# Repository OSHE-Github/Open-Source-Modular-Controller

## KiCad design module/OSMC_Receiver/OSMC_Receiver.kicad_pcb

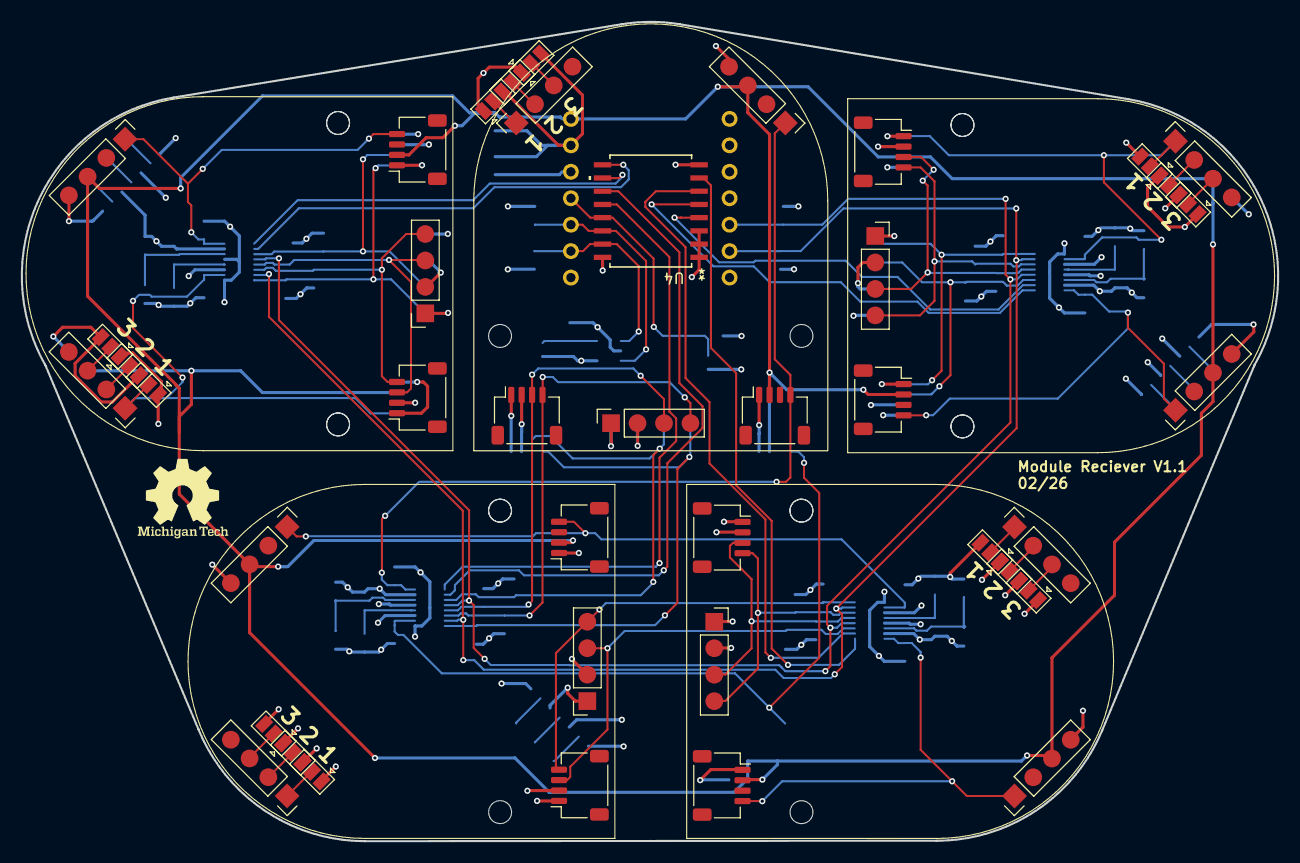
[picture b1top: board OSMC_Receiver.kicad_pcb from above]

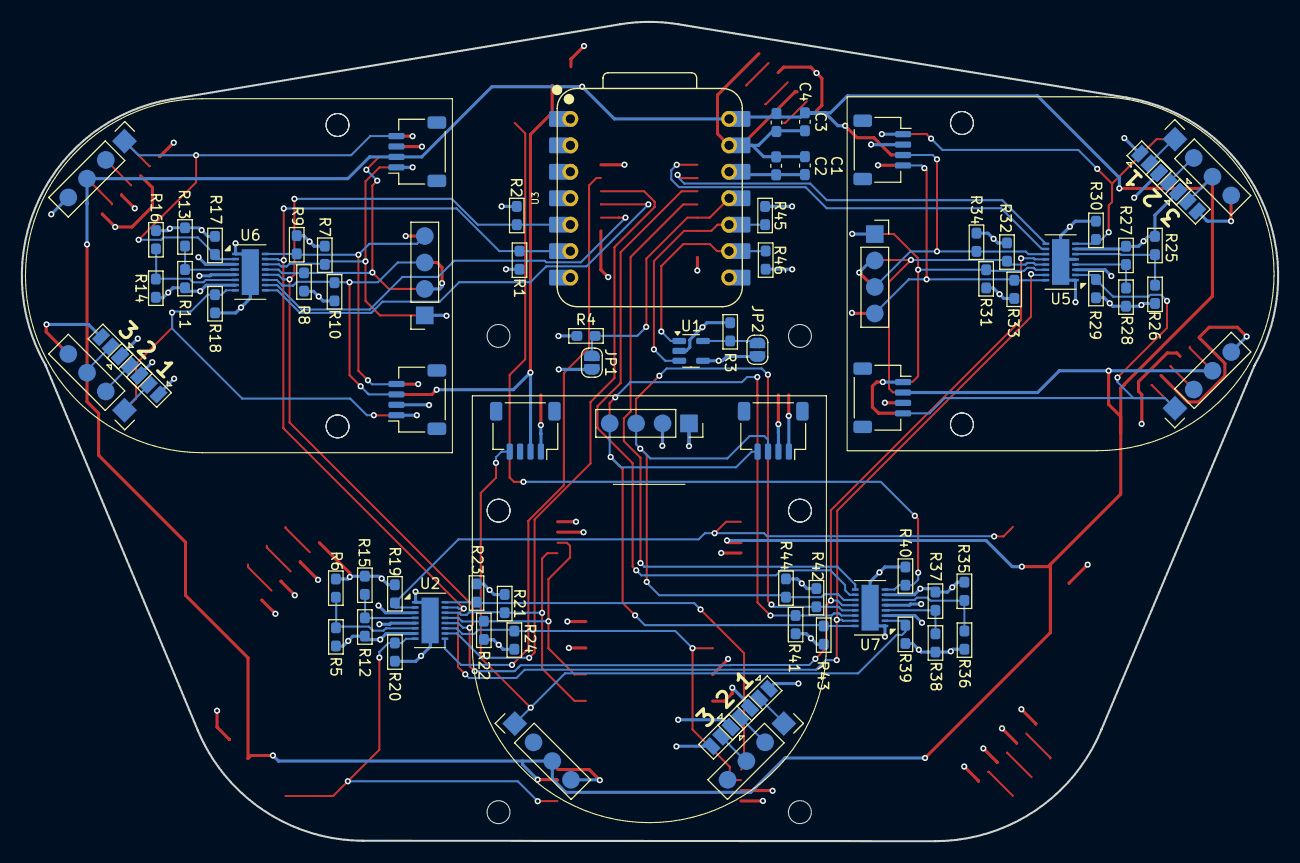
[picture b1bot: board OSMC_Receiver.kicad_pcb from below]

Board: 4 copper layers, 120.7 x 78.7 mm, 91 parts (70 on the bottom side), 73 nets.

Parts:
C1, C2: .1 u; C_0603_1608Metric_Pad1.08x0.95mm_HandSolder
C3, C4: C; C_0603_1608Metric_Pad1.08x0.95mm_HandSolder
JP1: int; SolderJumper-2_P1.3mm_Open_RoundedPad1.0x1.5mm
JP2: WP; SolderJumper-2_P1.3mm_Open_RoundedPad1.0x1.5mm
JP3, JP4, JP5, JP6, JP7, JP8, JP9, JP10, JP11, JP12, JP13, JP14, JP15, JP16, JP17, JP18, JP19, JP20, JP21, JP22, JP23, JP24, JP25, JP26: SolderJumper_3_Open; SolderJumper-3_P1.3mm_Open_Pad1.0x1.5mm
R1, R2, R7, R8, R9, R10, R17, R18, R19, R20, R21, R22, R23, R24, R29, R30, R31, R32, R33, R34, R39, R40, R41, R42, R43, R44, R45, R46: 10k; R_0603_1608Metric_Pad1.05x0.95mm_HandSolder
R3, R4: 100k; R_0603_1608Metric_Pad1.05x0.95mm_HandSolder
R5, R11: 976k; R_0603_1608Metric_Pad1.05x0.95mm_HandSolder
R6: 182k; R_0603_1608Metric_Pad1.05x0.95mm_HandSolder
R12: 1M; R_0603_1608Metric_Pad1.05x0.95mm_HandSolder
R13: 102k; R_0603_1608Metric_Pad1.05x0.95mm_HandSolder
R14: R; R_0603_1608Metric_Pad1.05x0.95mm_HandSolder
R15: 280k; R_0603_1608Metric_Pad1.05x0.95mm_HandSolder
R16: 0; R_0603_1608Metric_Pad1.05x0.95mm_HandSolder
R25, R27, R35, R37: 1000k; R_0603_1608Metric_Pad1.05x0.95mm_HandSolder
R26: 392k; R_0603_1608Metric_Pad1.05x0.95mm_HandSolder
R28: 523k; R_0603_1608Metric_Pad1.05x0.95mm_HandSolder
R36: 681k; R_0603_1608Metric_Pad1.05x0.95mm_HandSolder
R38: 887k; R_0603_1608Metric_Pad1.05x0.95mm_HandSolder
U1: 24AA02-OT; SOT-23-5
U2, U5, U6, U7: LTC4317; DFN-16-1EP_3x5mm_P0.5mm_EP1.66x4.4mm
U3: XIAO-ESP32-S3-DIP
U4: PCF8574DWR; DW16-L
U13, U14, U15, U16, U17, U18, U19, U20: OSMC Module Board; Module standard pin large outline

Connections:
+5V: C3.1, C4.1, U3.14 (5V), U13.10 (5V), U13.15 (5V), U14.10 (5V), U14.15 (5V), U15.10 (5V), U15.15 (5V), U16.10 (5V), U16.15 (5V), U17.10 (5V), U17.15 (5V), U18.10 (5V), U18.15 (5V), U19.10 (5V), U19.15 (5V), U20.10 (5V), U20.15 (5V)
/INT: JP1.1 (A), R4.2, U3.11 (PA6_A10_D10_MOSI), U4.13 (~INT)
/Modules/EN0: R18.2, U6.8 (ENABLE1), U13.12 (Det), U13.13 (Det)
/Modules/EN1: R17.2, U6.2 (ENABLE2), U15.12 (Det), U15.13 (Det)
/Modules/EN2: R20.2, U2.8 (ENABLE1), U16.12 (Det), U16.13 (Det)
/Modules/EN3: R19.2, U2.2 (ENABLE2), U18.12 (Det), U18.13 (Det)
/Modules/EN4: R30.2, U5.8 (ENABLE1), U17.12 (Det), U17.13 (Det)
/Modules/EN5: R29.2, U5.2 (ENABLE2), U20.12 (Det), U20.13 (Det)
/Modules/EN6: R40.2, U7.8 (ENABLE1), U14.12 (Det), U14.13 (Det)
/Modules/EN7: R39.2, U7.2 (ENABLE2), U19.12 (Det), U19.13 (Det)
/Modules/P0: U4.4 (P0), U6.10 (READY1)
/Modules/P1: U4.5 (P1), U6.9 (READY2)
/Modules/P2: U2.10 (READY1), U4.6 (P2)
/Modules/P3: U2.9 (READY2), U4.7 (P3)
/Modules/P4: U4.9 (P4), U5.10 (READY1)
/Modules/P5: U4.10 (P5), U5.9 (READY2)
/Modules/P6: U4.11 (P6), U7.10 (READY1)
/Modules/P7: U4.12 (P7), U7.9 (READY2)
/Modules/SCL0: R7.2, U6.14 (SCLOUT1), U13.4 (SCL), U13.8 (SCL)
/Modules/SCL1: R9.2, U6.16 (SCLOUT2), U15.4 (SCL), U15.8 (SCL)
/Modules/SCL2: R21.2, U2.14 (SCLOUT1), U16.4 (SCL), U16.8 (SCL)
/Modules/SCL3: R23.2, U2.16 (SCLOUT2), U18.4 (SCL), U18.8 (SCL)
/Modules/SCL4: R31.2, U5.14 (SCLOUT1), U17.4 (SCL), U17.8 (SCL)
/Modules/SCL5: R33.2, U5.16 (SCLOUT2), U20.4 (SCL), U20.8 (SCL)
/Modules/SCL6: R41.2, U7.14 (SCLOUT1), U14.4 (SCL), U14.8 (SCL)
/Modules/SCL7: R43.2, U7.16 (SCLOUT2), U19.4 (SCL), U19.8 (SCL)
/Modules/SDA0: R8.2, U6.13 (SDAOUT1), U13.3 (SDA), U13.7 (SDA)
/Modules/SDA1: R10.2, U6.11 (SDAOUT2), U15.3 (SDA), U15.7 (SDA)
/Modules/SDA2: R22.2, U2.13 (SDAOUT1), U16.3 (SDA), U16.7 (SDA)
/Modules/SDA3: R24.2, U2.11 (SDAOUT2), U18.3 (SDA), U18.7 (SDA)
/Modules/SDA4: R32.2, U5.13 (SDAOUT1), U17.3 (SDA), U17.7 (SDA)
/Modules/SDA5: R34.2, U5.11 (SDAOUT2), U20.3 (SDA), U20.7 (SDA)
/Modules/SDA6: R42.2, U7.13 (SDAOUT1), U14.3 (SDA), U14.7 (SDA)
/Modules/SDA7: R44.2, U7.11 (SDAOUT2), U19.3 (SDA), U19.7 (SDA)
/SCL: R1.2, U2.15 (SCLIN), U3.6 (PA9_A5_D5_SCL), U5.15 (SCLIN), U6.15 (SCLIN), U7.15 (SCLIN)
/SCL1: R46.2, U1.1 (SCL), U3.9 (PA7_A8_D8_SCK), U4.15 (SDA)
/SDA: R2.2, U2.12 (SDAIN), U3.5 (PA8_A4_D4_SDA), U5.12 (SDAIN), U6.12 (SDAIN), U7.12 (SDAIN)
/SDA1: R45.2, U1.3 (SDA), U3.10 (PA5_A9_D9_MISO), U4.14 (SCL)
/wp: JP2.1 (A), R3.2, U1.5 (WP)
GND: C1.2, C2.2, C3.2, C4.2, JP3.3 (B), JP4.3 (B), JP5.3 (B), JP6.3 (B), JP7.3 (B), JP8.3 (B), JP9.3 (B), JP10.3 (B), JP11.3 (B), JP12.3 (B), JP13.3 (B), JP14.3 (B), JP15.3 (B), JP16.3 (B), JP17.3 (B), JP18.3 (B), JP19.3 (B), JP20.3 (B), JP21.3 (B), JP22.3 (B), JP23.3 (B), JP24.3 (B), JP25.3 (B), JP26.3 (B), R3.1, R4.1, R6.2, R13.2, R15.2, R16.2, R17.1, R18.1, R19.1, R20.1, R26.2, R28.2, R29.1, R30.1, R36.2, R38.2, R39.1, R40.1, U1.2 (V_{SS}), U2.1 (GND), U2.3 (XORH2), U2.5 (XORH1), U2.17 (EP), U3.13 (GND), U4.1 (A0), U4.2 (A1), U4.3 (A2), U4.8 (GND), U5.1 (GND), U5.3 (XORH2), U5.5 (XORH1), U5.17 (EP), U6.1 (GND), U6.3 (XORH2), U6.5 (XORH1), U6.17 (EP), U7.1 (GND), U7.3 (XORH2), U7.5 (XORH1), U7.17 (EP), U13.1 (Gnd), U13.5 (Gnd), U13.9 (Gnd), U13.16 (GND), U14.1 (Gnd), U14.5 (Gnd), U14.9 (Gnd), U14.16 (GND), U15.1 (Gnd), U15.5 (Gnd), U15.9 (Gnd), U15.16 (GND), U16.1 (Gnd), U16.5 (Gnd), U16.9 (Gnd), U16.16 (GND), U17.1 (Gnd), U17.5 (Gnd), U17.9 (Gnd), U17.16 (GND), U18.1 (Gnd), U18.5 (Gnd), U18.9 (Gnd), U18.16 (GND), U19.1 (Gnd), U19.5 (Gnd), U19.9 (Gnd), U19.16 (GND), U20.1 (Gnd), U20.5 (Gnd), U20.9 (Gnd), U20.16 (GND)
unnamed: JP3.2 (C), U16.18 (A3)
unnamed: JP4.2 (C), U16.19 (A2)
unnamed: JP5.2 (C), U16.20 (A1)
unnamed: JP6.2 (C), U15.18 (A3)
unnamed: JP7.2 (C), U15.19 (A2)
unnamed: JP8.2 (C), U15.20 (A1)
unnamed: JP9.2 (C), U13.18 (A3)
unnamed: JP10.2 (C), U13.19 (A2)
unnamed: JP11.2 (C), U13.20 (A1)
unnamed: JP12.2 (C), U18.18 (A3)
unnamed: JP13.2 (C), U18.19 (A2)
unnamed: JP14.2 (C), U18.20 (A1)
unnamed: JP15.2 (C), U19.18 (A3)
unnamed: JP16.2 (C), U19.19 (A2)
unnamed: JP17.2 (C), U19.20 (A1)
unnamed: JP18.2 (C), U17.18 (A3)
unnamed: JP19.2 (C), U17.19 (A2)
unnamed: JP20.2 (C), U17.20 (A1)
unnamed: JP21.2 (C), U20.18 (A3)
unnamed: JP22.2 (C), U20.19 (A2)
unnamed: JP23.2 (C), U20.20 (A1)
unnamed: JP24.2 (C), U14.18 (A3)
unnamed: JP25.2 (C), U14.19 (A2)
unnamed: JP26.2 (C), U14.20 (A1)
unnamed: R5.2, R6.1, U2.6 (XORL1)
unnamed: R12.2, R15.1, U2.4 (XORL2)
unnamed: R25.2, R26.1, U5.6 (XORL1)
unnamed: R27.2, R28.1, U5.4 (XORL2)
unnamed: R14.2, R16.1, U6.6 (XORL1)
unnamed: R11.2, R13.1, U6.4 (XORL2)
unnamed: R35.2, R36.1, U7.6 (XORL1)
unnamed: R37.2, R38.1, U7.4 (XORL2)
VDD: C1.1, C2.1, JP1.2 (B), JP2.2 (B), JP3.1 (A), JP4.1 (A), JP5.1 (A), JP6.1 (A), JP7.1 (A), JP8.1 (A), JP9.1 (A), JP10.1 (A), JP11.1 (A), JP12.1 (A), JP13.1 (A), JP14.1 (A), JP15.1 (A), JP16.1 (A), JP17.1 (A), JP18.1 (A), JP19.1 (A), JP20.1 (A), JP21.1 (A), JP22.1 (A), JP23.1 (A), JP24.1 (A), JP25.1 (A), JP26.1 (A), R1.1, R2.1, R5.1, R7.1, R8.1, R9.1, R10.1, R11.1, R12.1, R14.1, R21.1, R22.1, R23.1, R24.1, R25.1, R27.1, R31.1, R32.1, R33.1, R34.1, R35.1, R37.1, R41.1, R42.1, R43.1, R44.1, R45.1, R46.1, U1.4 (V_{CC}), U2.7 (VCC), U3.12 (3V3), U4.16 (VDD), U5.7 (VCC), U6.7 (VCC), U7.7 (VCC), U13.2 (Vdd), U13.6 (Vdd), U14.2 (Vdd), U14.6 (Vdd), U15.2 (Vdd), U15.6 (Vdd), U16.2 (Vdd), U16.6 (Vdd), U17.2 (Vdd), U17.6 (Vdd), U18.2 (Vdd), U18.6 (Vdd), U19.2 (Vdd), U19.6 (Vdd), U20.2 (Vdd), U20.6 (Vdd)

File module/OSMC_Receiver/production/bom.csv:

Designator,Footprint,Quantity,Value,LCSC Part #
"C1, C2",0603,2,.1 u,
"C3, C4",0603,2,C,
"R1, R10, R17, R18, R19, R2, R20, R21, R22, R23, R24, R29, R30, R31, R32, R33, R34, R39, R40, R41, R42, R43, R44, R45, R46, R7, R8, R9",0603,28,10k,
"R11, R5",0603,2,976k,
"R12, R6",0603,2,182k,
R13,0603,1,102k,
R14,0603,1,R,
R15,0603,1,280k,
R16,0603,1,0,
"R25, R27, R35, R37",0603,4,1000k,
R26,0603,1,392k,
R28,0603,1,523k,
"R3, R4",0603,2,100k,
R36,0603,1,681k,
R38,0603,1,887k,
U1,SOT-23-5,1,24AA02-OT,
"U13, U14, U15, U16, U17, U18, U19, U20",Module standard pin large outline,8,OSMC Module Board,
"U2, U5, U6, U7",DFN-16-1EP_3x5mm_P0.5mm_EP1.66x4.4mm,4,LTC4317,
U3,XIAO-ESP32-S3-DIP,1,XIAO-ESP32-S3-DIP,
U4,DW16-L,1,PCF8574DWR,
